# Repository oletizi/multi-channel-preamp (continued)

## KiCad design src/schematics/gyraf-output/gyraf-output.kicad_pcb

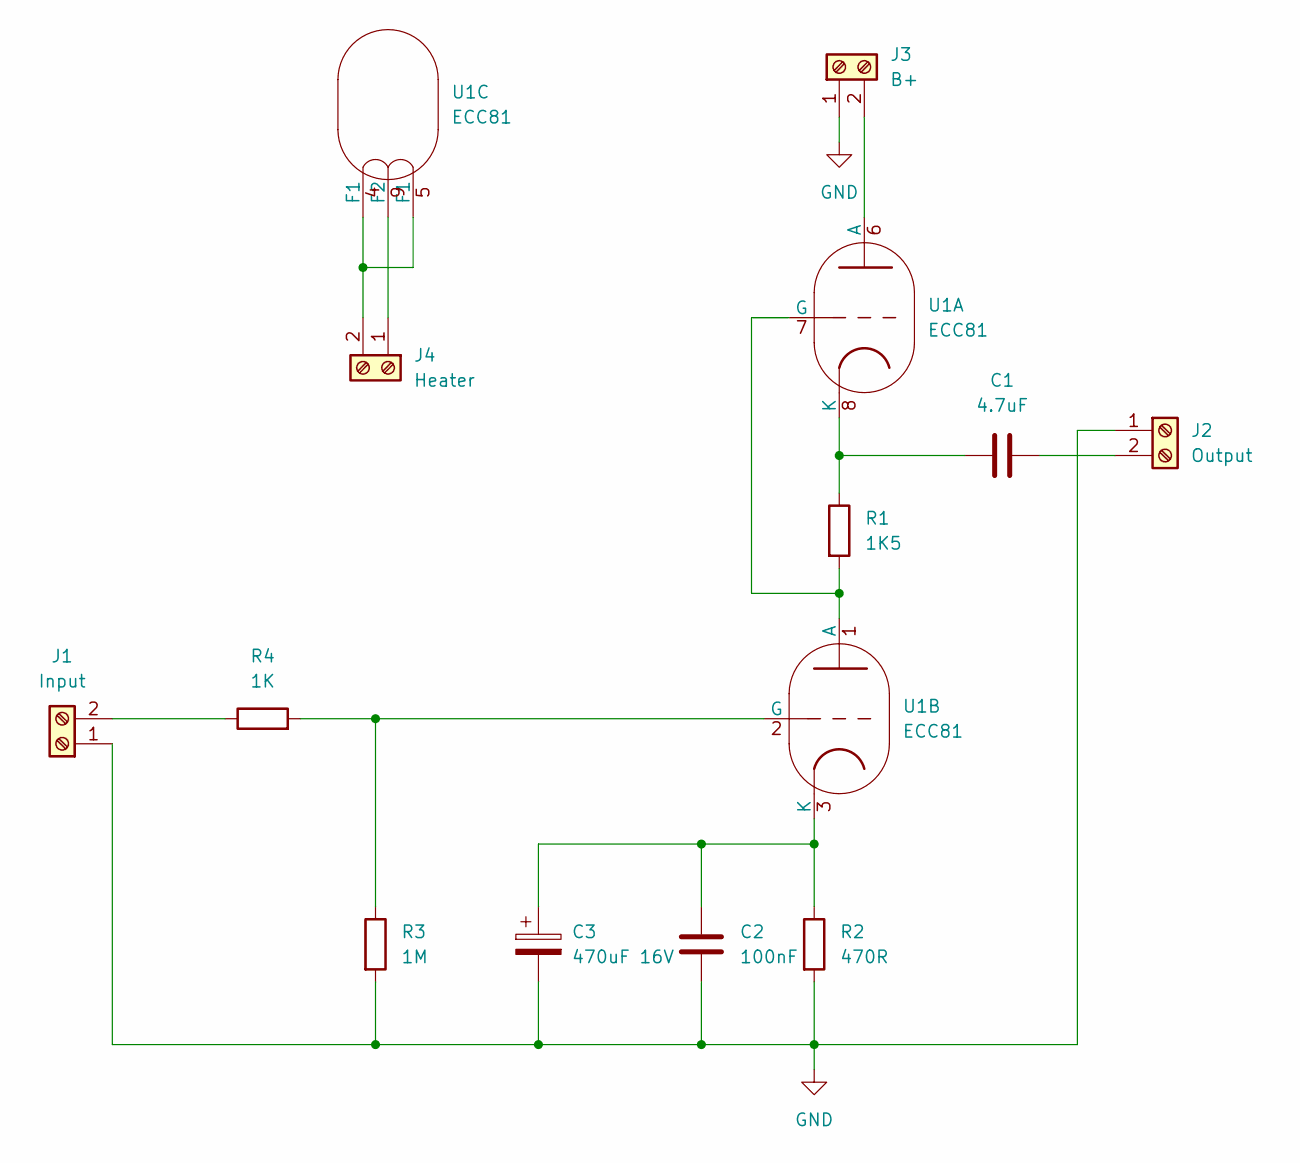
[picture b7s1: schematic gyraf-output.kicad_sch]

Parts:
C1: 4.7uF; C_Axial_L12.0mm_D8.5mm_P15.00mm_Horizontal Fat Pad
C2: 100nF; C_Axial_L12.0mm_D8.5mm_P15.00mm_Horizontal Fat Pad
C3: 470uF 16V; CP_Axial_L37.0mm_D13.0mm_P43.00mm_Horizontal_Fat_Pad
J1: Input; TerminalBlock_Phoenix_MKDS-1,5-2_1x02_P5.00mm_Horizontal Fa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
J2: Output; TerminalBlock_Phoenix_MKDS-1,5-2_1x02_P5.00mm_Horizontal Fa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
J3: B+; TerminalBlock_Phoenix_MKDS-1,5-2_1x02_P5.00mm_Horizontal Fa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
J4: Heater; TerminalBlock_Phoenix_MKDS-1,5-2_1x02_P5.00mm_Horizontal Fa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
R1: 1K5; R_Axial_DIN0411_L9.9mm_D3.6mm_P12.70mm_Horizontal Fat Pad
R2: 470R; R_Axial_DIN0411_L9.9mm_D3.6mm_P12.70mm_Horizontal Fat Pad
R3: 1M; R_Axial_DIN0411_L9.9mm_D3.6mm_P12.70mm_Horizontal Fat Pad
R4: 1K; R_Axial_DIN0411_L9.9mm_D3.6mm_P12.70mm_Horizontal Fat Pad
U1: ECC81; BELTON_VT9-PT Fat Pad

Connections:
GND: C2.2, C3.2, J1.1, J2.1, J3.1, R2.2, R3.2
unnamed: J1.2, R4.1
unnamed: C1.2, J2.2
unnamed: J3.2, U1.6 (A)
unnamed: J4.1, U1.9 (F2)
unnamed: J4.2, U1.4 (F1), U1.5 (F1)
unnamed: R1.2, U1.1 (A), U1.7 (G)
unnamed: C1.1, R1.1, U1.8 (K)
unnamed: R3.1, R4.2, U1.2 (G)
unnamed: C2.1, C3.1, R2.1, U1.3 (K)

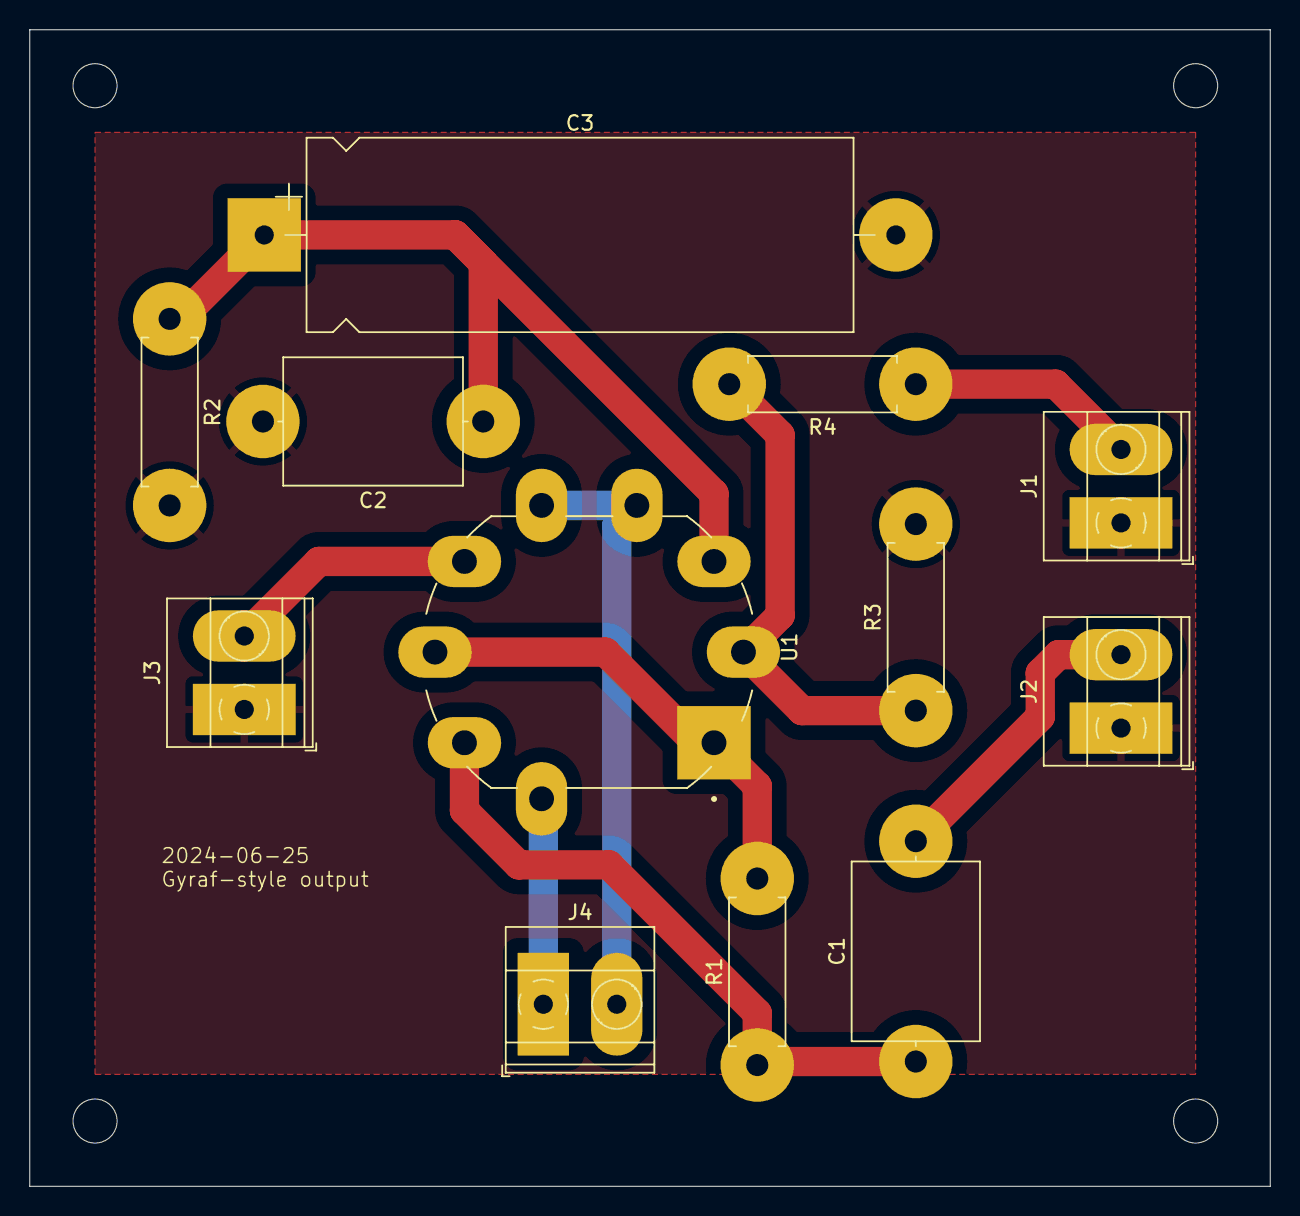
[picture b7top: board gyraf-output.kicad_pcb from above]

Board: 2 copper layers, 84.5 x 78.7 mm, 12 parts (0 on the bottom side), 10 nets.

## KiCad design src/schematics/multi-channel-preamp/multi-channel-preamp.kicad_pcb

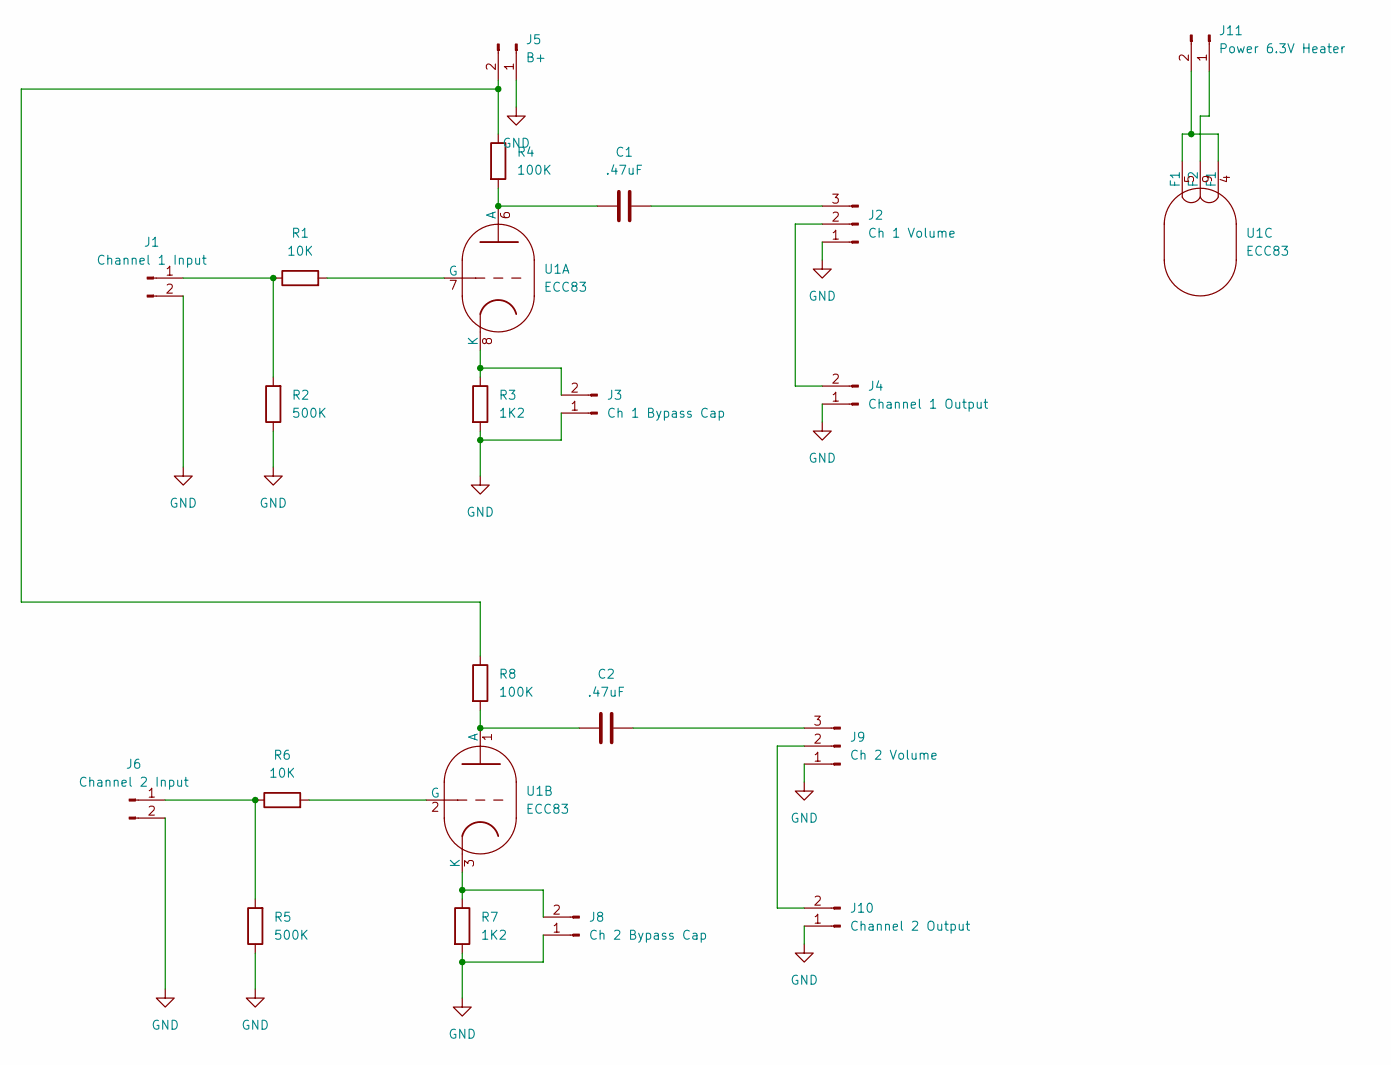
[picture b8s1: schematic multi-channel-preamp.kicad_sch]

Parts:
C1, C2: .47uF; C_Axial_L22.0mm_D9.5mm_P27.50mm_Horizontal
J1: Channel 1 Input; TerminalBlock_Phoenix_MKDS-1,5-2_1x02_P5.00mm_Horizontal Fa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
J2: Ch 1 Volume; TerminalBlock_Phoenix_MKDS-1,5-3_1x03_P5.00mm_Horizontal Fa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
J3: Ch 1 Bypass Cap; TerminalBlock_Phoenix_MKDS-1,5-2_1x02_P5.00mm_Horizontal Fa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
J4: Channel 1 Output; TerminalBlock_Phoenix_MKDS-1,5-2_1x02_P5.00mm_Horizontal Fa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
J5: B+; TerminalBlock_Phoenix_MKDS-1,5-2_1x02_P5.00mm_Horizontal Fa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
J6: Channel 2 Input; TerminalBlock_Phoenix_MKDS-1,5-2_1x02_P5.00mm_Horizontal Fa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
J8: Ch 2 Bypass Cap; TerminalBlock_Phoenix_MKDS-1,5-2_1x02_P5.00mm_Horizontal Fa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
J9: Ch 2 Volume; TerminalBlock_Phoenix_MKDS-1,5-3_1x03_P5.00mm_Horizontal Fa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
J10: Channel 2 Output; TerminalBlock_Phoenix_MKDS-1,5-2_1x02_P5.00mm_Horizontal Fa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
J11: Power 6.3V Heater; TerminalBlock_Phoenix_MKDS-1,5-2_1x02_P5.00mm_Horizontal Fa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
R1, R6: 10K; R_Axial_DIN0207_L6.3mm_D2.5mm_P10.16mm_Horizontal
R2, R5: 500K; R_Axial_DIN0207_L6.3mm_D2.5mm_P10.16mm_Horizontal
R3, R7: 1K2; R_Axial_DIN0309_L9.0mm_D3.2mm_P12.70mm_Horizontal
R4, R8: 100K; R_Axial_DIN0309_L9.0mm_D3.2mm_P12.70mm_Horizontal
U1: ECC83; BELTON_VT9-PT Fat Pad

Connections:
GND: J1.2, J2.1, J3.1, J4.1, J5.1, J6.2, J8.1, J9.1, J10.1, R2.1, R3.2, R5.1, R7.2
unnamed: J1.1, R1.1, R2.2
unnamed: J2.2, J4.2
unnamed: C1.2, J2.3
unnamed: J3.2, R3.1, U1.8 (K)
unnamed: J5.2, R4.1, R8.1
unnamed: J6.1, R5.2, R6.1
unnamed: J8.2, R7.1, U1.3 (K)
unnamed: C2.2, J9.3
unnamed: J9.2, J10.2
unnamed: J11.1, U1.9 (F2)
unnamed: J11.2, U1.4 (F1), U1.5 (F1)
unnamed: C1.1, R4.2, U1.6 (A)
unnamed: R1.2, U1.7 (G)
unnamed: C2.1, R8.2, U1.1 (A)
unnamed: R6.2, U1.2 (G)

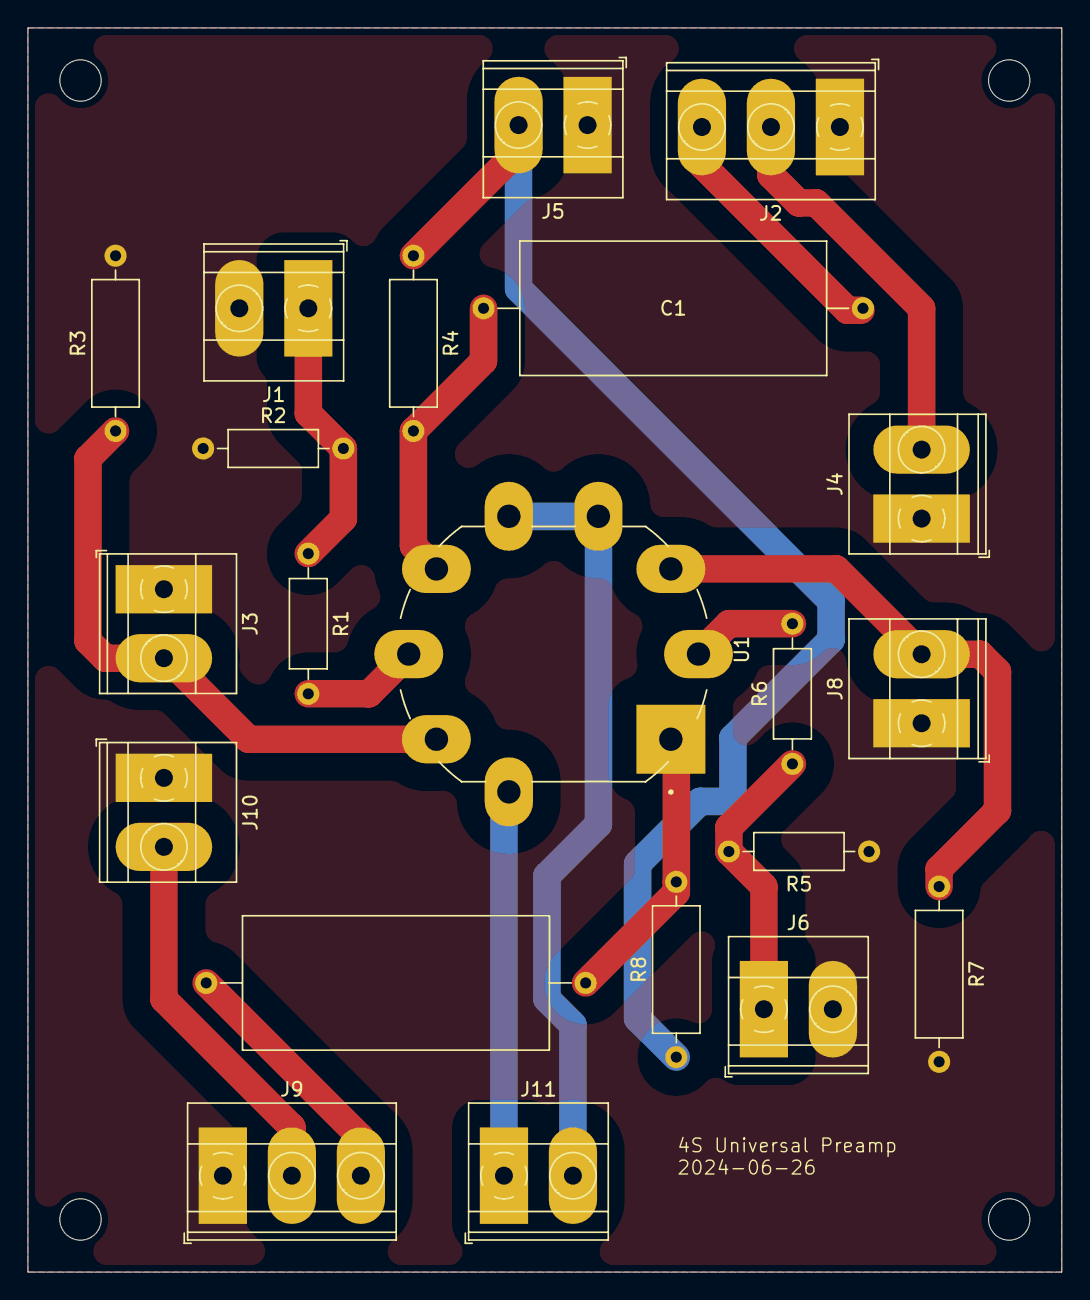
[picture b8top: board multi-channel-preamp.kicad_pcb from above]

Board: 2 copper layers, 74.9 x 90.2 mm, 21 parts (0 on the bottom side), 16 nets.

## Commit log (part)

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2024-06-12 exported gerbers
2024-06-12 updated gerbers with origin
2024-06-12 trying origin again
2024-06-12 trying svg
2024-06-12 pcb updates
2024-06-22 tapeop preamp output
2024-06-22 gitignore
2024-06-22 git cleanup
2024-07-04 big add
2024-07-04 - First pass of pultec-cut-low
2024-07-04 - pultec-cut-low toner transfer art
2024-07-05 - pultec-cut-high schematic, pcb, and toner transfer art
2024-07-06 - merged high & low cut and boost to a single schematic/pcb
2024-07-06 - fixed pultec-boost-high name
2024-07-10 - fixed unrouted traces
2024-07-12 - fixed issue with hierarchical label - fixed unrouted trace related to issue with hierarchical label - Updated PCB identifier in front copper and front fab layers to use variables instead of hard-co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
2024-07-12 - updated PCB art to revision 3
2024-07-12 - added README.md
2024-07-17 - re-worked the mid-range - exported gerbers for PCB manufacture
2024-07-24 - added breakout board for inductors
2025-05-30 Added local copies of Ian Thompson-Bell's documentation in case it disappears from the internet
2025-10-26 docs(pultec): add modular design documentation and BOMs
2025-10-26 docs(claude): add specialized agents and project instructions
2025-10-26 Prompt is too long
2025-10-26 Perfect! I can see that the staged changes include:
2025-10-27 docs(reference): add Ian Thompson-Bell Pultec 3-band documentation and resolve low-boost capacitor discrepancy
